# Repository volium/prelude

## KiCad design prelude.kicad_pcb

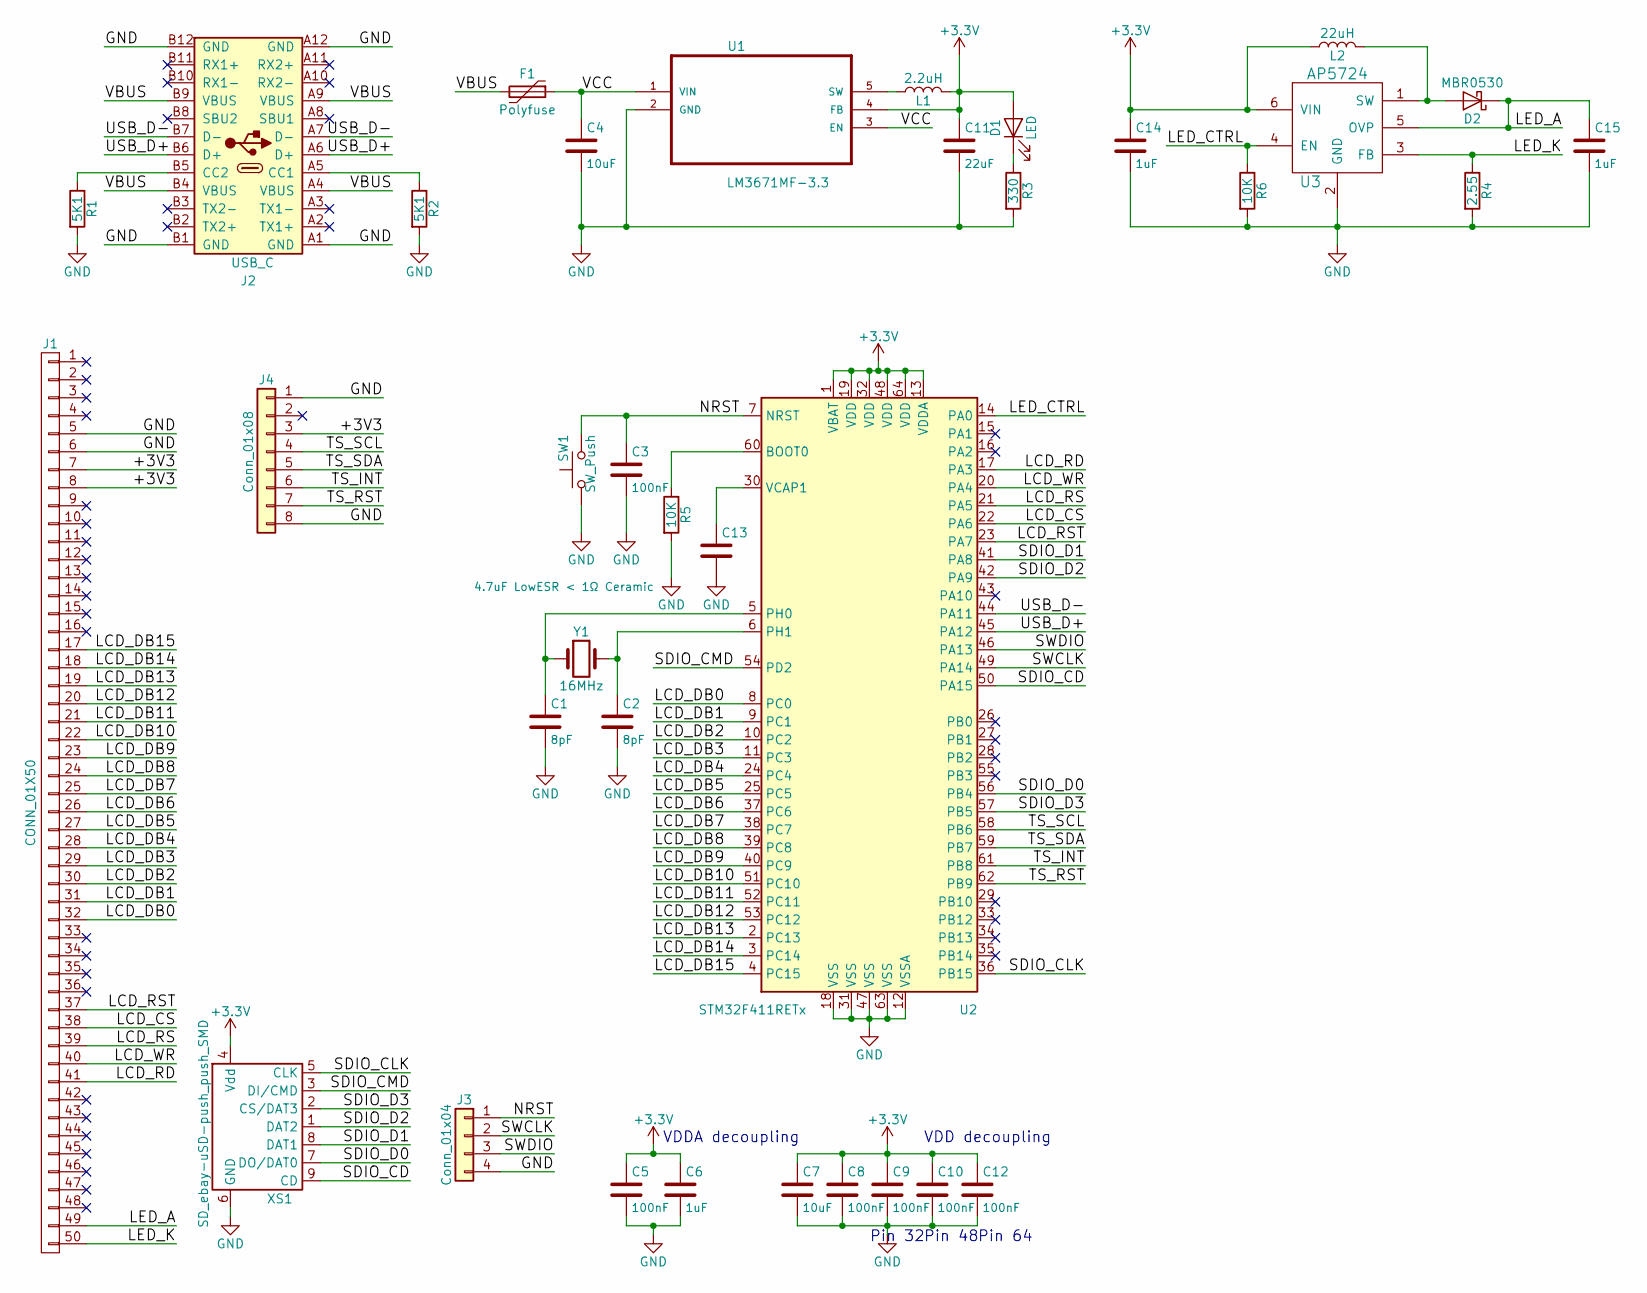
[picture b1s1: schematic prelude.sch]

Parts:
C1, C2: 8pF; C_0805_2012Metric
C3, C5, C8, C9, C10, C12: 100nF; C_0805_2012Metric
C4, C7: 10uF; C_0805_2012Metric
C6, C14, C15: 1uF; C_0805_2012Metric
C11: 22uF; C_0805_2012Metric
C13: 4.7uF LowESR < 1Ω Ceramic; C_0805_2012Metric
D1: LED; LED_0805_2012Metric
D2: MBR0530; D_SOD-123
F1: Polyfuse; MF-PSMF050X
J1: CONN_01X50; 62684-502100ALF
J2: USB_C; D0-9062-005LG
J3: Conn_01x04; M20-8890445
J4: Conn_01x08; WE_68710814022
L1: 2.2uH; L_Taiyo-Yuden_NR-24xx_HandSoldering
L2: 22uH; L_Taiyo-Yuden_NR-30xx_HandSoldering
R1, R2: 5K1; R_0805_2012Metric
R3: 330; R_0805_2012Metric
R4: 2.55; R_0805_2012Metric
R5, R6: 10K; R_0805_2012Metric
SW1: SW_Push; SW_SPST_PTS645
U1: LM3671MF-3.3; SOT-23-5_HandSoldering
U2: STM32F411RETx; LQFP-64_10x10mm_P0.5mm
U3: AP5724; SOT-23-6_Handsoldering
XS1: SD_ebay-uSD-push_push_SMD; Conn_uSDcard
Y1: 16MHz; Crystal_SMD_5032-2Pin_5.0x3.2mm

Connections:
/LCD_CS: J1.38, U2.22 (PA6)
/LCD_DB0: J1.32, U2.8 (PC0)
/LCD_DB1: J1.31, U2.9 (PC1)
/LCD_DB2: J1.30, U2.10 (PC2)
/LCD_DB3: J1.29, U2.11 (PC3)
/LCD_DB4: J1.28, U2.24 (PC4)
/LCD_DB5: J1.27, U2.25 (PC5)
/LCD_DB6: J1.26, U2.37 (PC6)
/LCD_DB7: J1.25, U2.38 (PC7)
/LCD_DB8: J1.24, U2.39 (PC8)
/LCD_DB9: J1.23, U2.40 (PC9)
/LCD_DB10: J1.22, U2.51 (PC10)
/LCD_DB11: J1.21, U2.52 (PC11)
/LCD_DB12: J1.20, U2.53 (PC12)
/LCD_DB13: J1.19, U2.2 (PC13)
/LCD_DB14: J1.18, U2.3 (PC14)
/LCD_DB15: J1.17, U2.4 (PC15)
/LCD_RD: J1.41, U2.17 (PA3)
/LCD_RS: J1.39, U2.21 (PA5)
/LCD_RST: J1.37, U2.23 (PA7)
/LCD_WR: J1.40, U2.20 (PA4)
/LED_A: C15.1, D2.1 (K), J1.49, U3.5 (OVP)
/LED_CTRL: R6.1, U2.14 (PA0), U3.4 (EN)
/LED_K: J1.50, R4.1, U3.3 (FB)
/NRST: C3.1, J3.1, SW1.2, U2.7 (NRST)
/SDIO_CD: U2.50 (PA15), XS1.9 (CD)
/SDIO_CLK: U2.36 (PB15), XS1.5 (CLK)
/SDIO_CMD: U2.54 (PD2), XS1.3 (DI/CMD)
/SDIO_D0: U2.56 (PB4), XS1.7 (DO/DAT0)
/SDIO_D1: U2.41 (PA8), XS1.8 (DAT1)
/SDIO_D2: U2.42 (PA9), XS1.1 (DAT2)
/SDIO_D3: U2.57 (PB5), XS1.2 (CS/DAT3)
/SWCLK: J3.2, U2.49 (PA14)
/SWDIO: J3.3, U2.46 (PA13)
/TS_INT: J4.6, U2.61 (PB8)
/TS_RST: J4.7, U2.62 (PB9)
/TS_SCL: J4.4, U2.58 (PB6)
/TS_SDA: J4.5, U2.59 (PB7)
/USB_D+: J2.A6 (D+), J2.B6 (D+), U2.45 (PA12)
/USB_D-: J2.A7 (D-), J2.B7 (D-), U2.44 (PA11)
/VBUS: F1.2, J2.A4 (VBUS), J2.A9 (VBUS), J2.B4 (VBUS), J2.B9 (VBUS)
/VCC: C4.1, F1.1, U1.1 (VIN), U1.3 (EN)
GND: C1.2, C2.2, C3.2, C4.2, C5.2, C6.2, C7.2, C8.2, C9.2, C10.2, C11.2, C12.2, C13.2, C14.2, C15.2, J1.5, J1.6, J2.A1 (GND), J2.A12 (GND), J2.B1 (GND), J2.B12 (GND), J3.4, J4.1, J4.8, R1.2, R2.2, R3.2, R4.2, R5.2, R6.2, SW1.1, U1.2 (GND), U2.12 (VSSA), U2.18 (VSS), U2.31 (VSS), U2.47 (VSS), U2.63 (VSS), U3.2 (GND), XS1.6 (GND)
unnamed: C1.1, U2.5 (PH0), Y1.1
unnamed: C2.1, U2.6 (PH1), Y1.2
unnamed: C13.1, U2.30 (VCAP1)
unnamed: D1.1 (K), R3.1
unnamed: D2.2 (A), L2.2, U3.1 (SW)
unnamed: J2.A5 (CC1), R2.1
unnamed: J2.B5 (CC2), R1.1
unnamed: L1.1, U1.5 (SW)
unnamed: R5.1, U2.60 (BOOT0)

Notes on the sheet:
VDDA decoupling
VDD decoupling
Pin 64
Pin 48
Pin 32

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
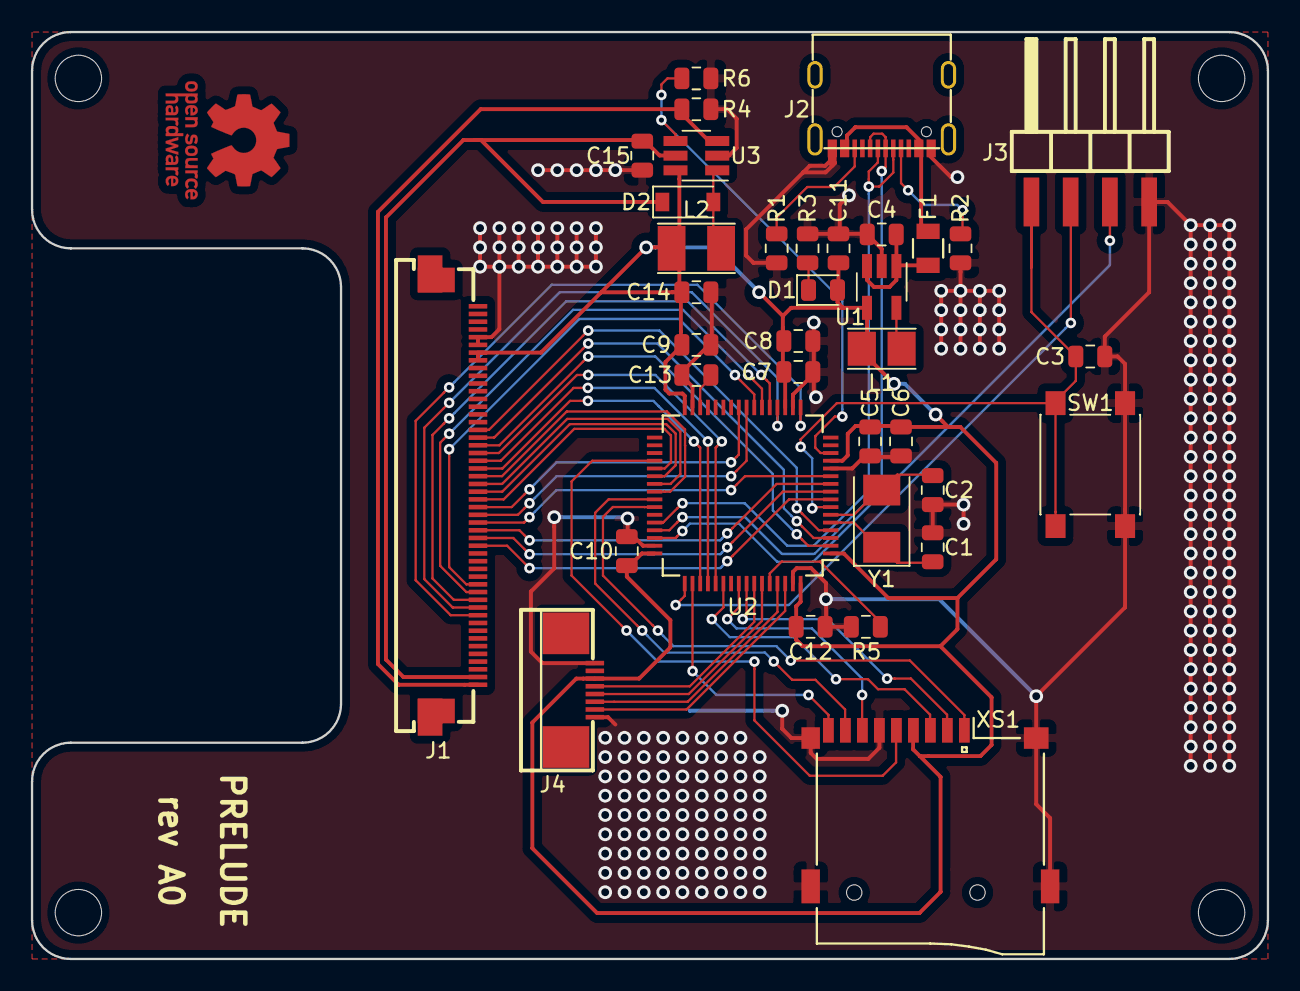
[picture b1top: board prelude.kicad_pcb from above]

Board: 2 copper layers, 80.0 x 60.0 mm, 36 parts (0 on the bottom side), 53 nets.

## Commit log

2017-08-16 First commit
    Adding project files for prelude
2017-08-16 Create LICENSE
2017-08-16 Adds MCU and 50 pin connector to schematic
    Adds STM32F103RETx to schematic
    Adds STM32 library to project
2017-08-17 Adds KD040WVFBD003-C005A SPEC V1.0.pdf
2017-08-19 Adds main 3.3 power supply based on LM3671MF
    Removed and added back 50-in connector, after fixing grid alignment
2017-08-23 Updates USB connector to to USB C
    Added necessary connections and resistors (5.1K pulldown) to allow for device enumeration
2017-08-23 Updates schematic and project
    Adds passives and wires to MCU
    Adds switches library to project
2017-09-01 Several updates to schematic
    Adds decoupling capacitors
    Adds debug connector
    Adds values to several components
2017-09-01 Adds values to Crystal (16 MHz) and a one inductor (2.2 uH)
2017-09-01 Annotates components
2017-09-04 Several changes
    Ran CvPcb
    Added MicroSD card connector (Molex)
    Started PCB routing with MCU pin row pins 1-16 facing 50-pin LCD connector
2017-09-06 Moved to STM32F411RE
    Had to move to different MCU (STM32F411RE) because I2C bus was fixed to pins on B bus, which was used for LCD data bus, and SDIO was also fixed to C bus.
    Remapped LCD data bus to C bus since it allows having all other functionality (SDIO, I2C, USB) correctly mapped.
    Redid CvPcb and net generation.
    Started PCB routing with MCU pins 49-64 facing LCD connector.
2018-04-01 A lot of changes, just need to add more polish and clean up
2019-02-23 Updates project after loading with KiCad 5.0.2
    Replaced schematic symbols and pcb footprints with new versions
    Regenerated netlist after all changes
2019-02-27 Replaces passive components with regular (non-HandSolder) versions
2019-02-27 Replaces J2 Connector (USB-C) with new D0-9062-005LG (SMD 16 terminals)
2019-02-27 Updates prelude.kicad_pcb in latest version of KiCad (5.0.2)
    Replaced two tracks with one
2019-02-27 Updates to prelude.kicad_pcb
    Reloaded updated netlist, exchanged footprints, adjusted J2 connector and rerouted USB-C portion.
    Adds R6, which had not been imported before (by mistake)
2019-04-07 Fixes some routing issues
    One pwr track was too narrow
    Aligned vias for SDIO signals CMD, D0 and D3
2019-04-09 Final touches to prelude
    Added via stitching, fixed alignment issues, moved references in silkscreen, added OSH logo and project name and revision
    Updates main prelude.pro project file
2019-04-09 Adds more via stitching at the top of the board
2019-04-09 Adds project name and revision to back silk screen
2019-04-12 Adds gerber files, including zip file
2019-04-14 Minor update to schematic to include "F" in all values of capacitors
2019-04-14 Regenerates netlist based on previous change to schematic
2019-04-14 Updates layout after importing latest netlist with changes in schematic.
    Moved LED_A trace to be more like LED_K on its way to J1, recalculates fill zones.
2019-04-14 Updates project file with latest minimal changes
2019-04-14 Adds new BOM files generated via "bom_csv_grouped_by_value"
2019-04-17 Minor clean up of tracks
2019-04-28 Replaces Inductors (L1 and L2) with HandSoldering versions
2019-04-28 Replaces inductors with HandSoldering versions, recalculated fills, still need to adjust vias
2019-04-28 Adjusted vias and tracks with latest Inductor footprints (HandSoldering), removed row of vias
2019-04-28 Fixes via next to C10
2019-05-13 Properly rounds cutout corners based on SWARM project
